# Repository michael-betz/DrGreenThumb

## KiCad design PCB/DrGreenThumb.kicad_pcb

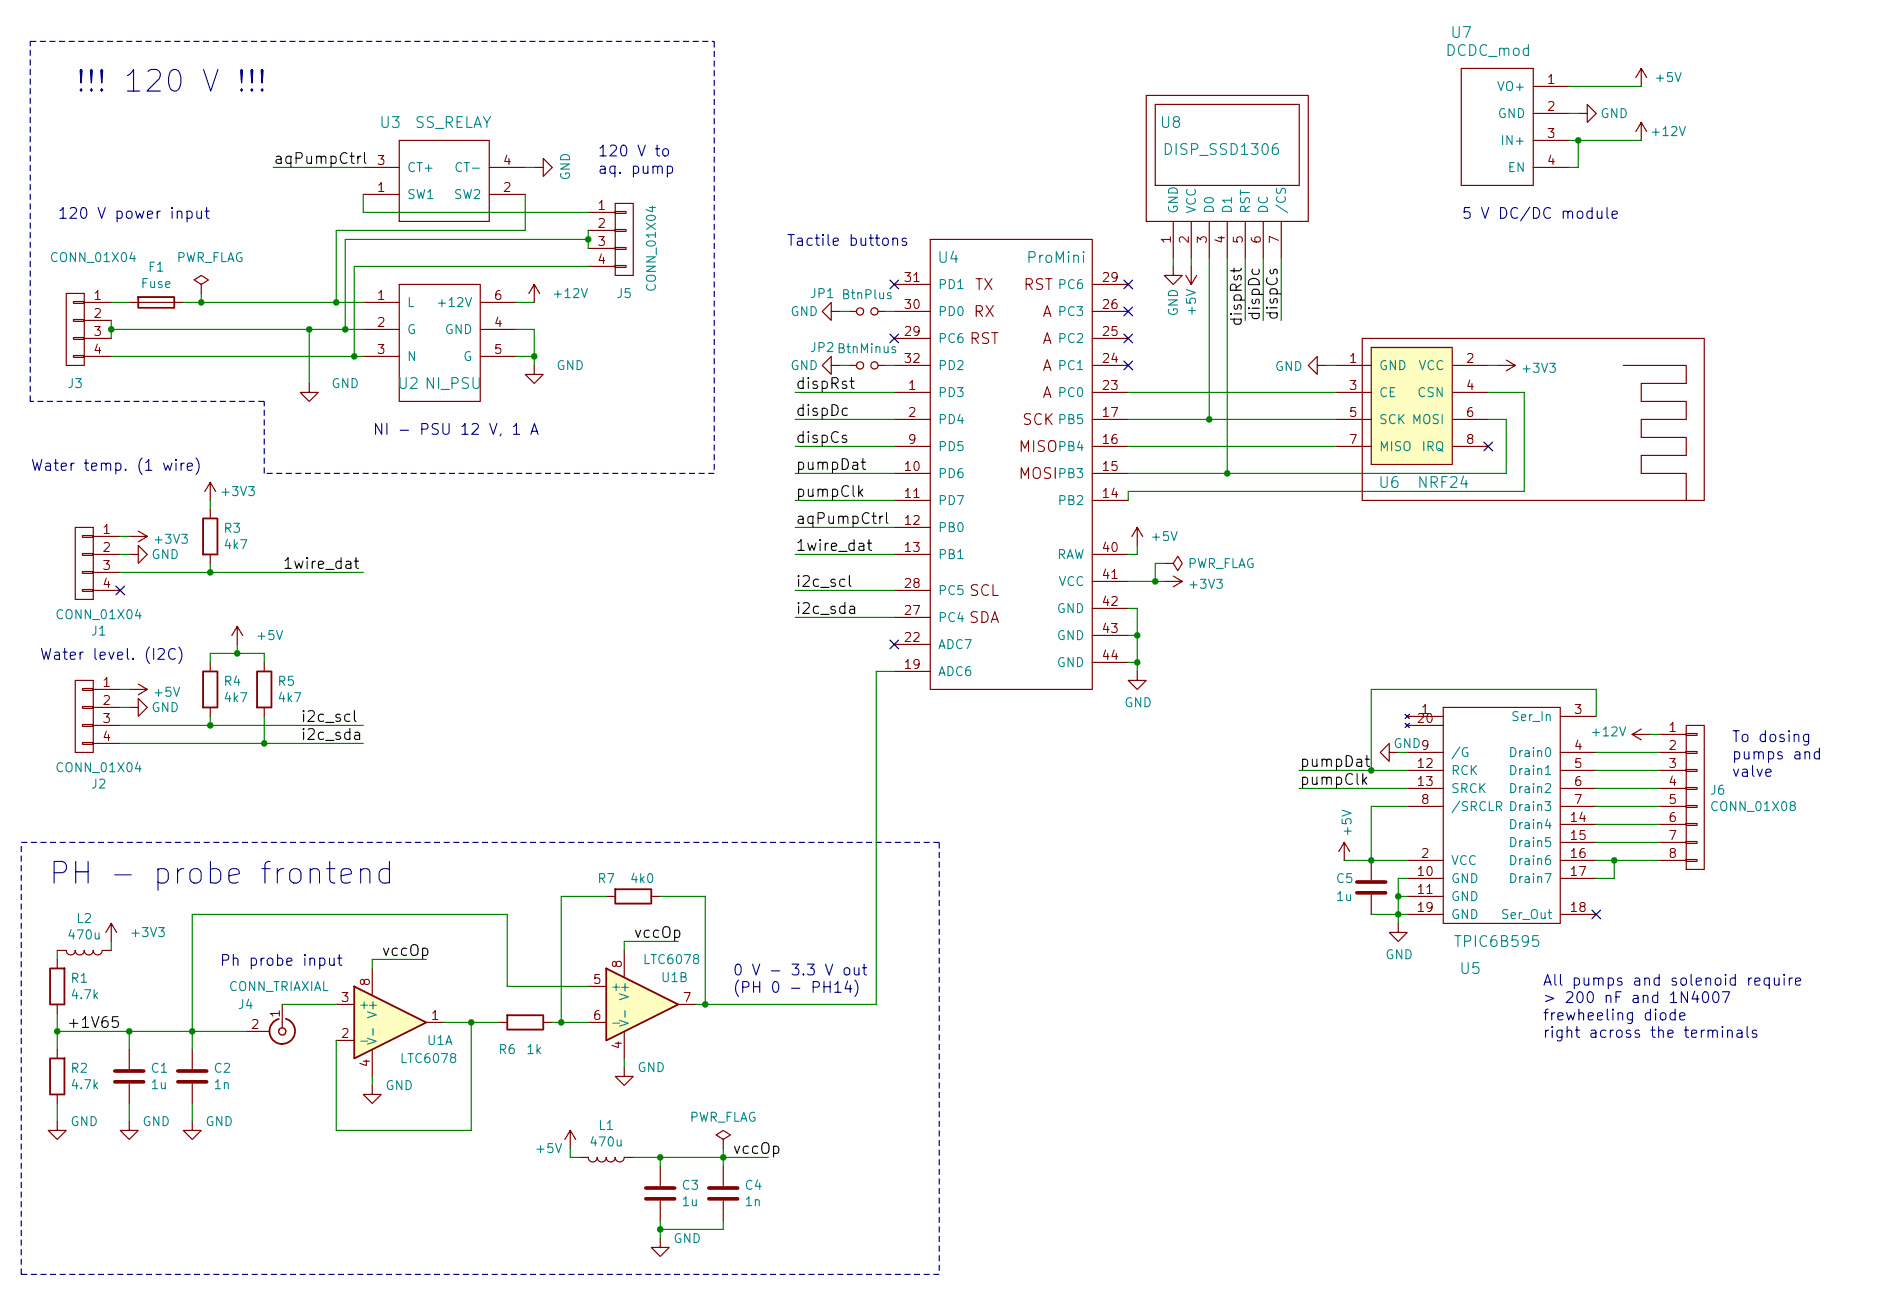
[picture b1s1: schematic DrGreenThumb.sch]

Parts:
C1, C3, C5: 1u; C_0805
C2, C4: 1n; C_0805
F1: Fuse; Fuseholder5x20_horiz_SemiClosed_Casing10x25mm
J1, J2, J3, J5: CONN_01X04; Pin_Header_Straight_1x04_Pitch2.54mm
J4: CONN_TRIAXIAL; bnc-ci
J6: CONN_01X08; Pin_Header_Straight_1x08_Pitch2.54mm
JP1: BtnPlus; ITT_TACT
JP2: BtnMinus; ITT_TACT
L1, L2: 470u; R_1210_HandSoldering
R1, R2: 4.7k; R_0805
R3, R4, R5: 4k7; R_0805
R6: 1k; R_0805
R7: 4k0; R_0805
U1: LTC6078; MSOP-8_3x3mm_Pitch0.65mm
U2: NI_PSU
U3: SS_RELAY
U4: ProMini; PRO_MINI
U5: TPIC6B595; DIP-20_W7.62mm
U6: NRF24
U7: DCDC_mod; ebay_dcdc
U8: DISP_SSD1306

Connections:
+3V3: J1.1, L2.1, R3.1, U4.41 (VCC), U6.2 (VCC)
+5V: C5.1, J2.1, L1.2, R4.1, R5.1, U4.40 (RAW), U5.2 (VCC), U5.8 (/SRCLR), U7.1 (VO+), U8.2 (VCC)
+12V: J6.1, U2.6 (+12V), U7.3 (IN+), U7.4 (EN)
/1wire_dat: J1.3, R3.2, U4.13 (PB1)
/+1V65: C1.1, C2.1, J4.2 (Ext), R1.1, R2.2, U1.5 (+)
/aqPumpCtrl: U3.3 (CT+), U4.12 (PB0)
/dispCs: U4.9 (PD5), U8.7 (/CS)
/dispDc: U4.2 (PD4), U8.6 (DC)
/dispRst: U4.1 (PD3), U8.5 (RST)
/i2c_scl: J2.3, R4.2, U4.28 (PC5)
/i2c_sda: J2.4, R5.2, U4.27 (PC4)
/pumpClk: U4.11 (PD7), U5.13 (SRCK)
/pumpDat: U4.10 (PD6), U5.3 (Ser_In), U5.12 (RCK)
/vccOp: C3.1, C4.1, L1.1, U1.8 (V+)
GND: C1.2, C2.2, C3.2, C4.2, C5.2, J1.2, J2.2, J3.2, J3.3, J5.2, J5.3, JP1.1, JP2.1, R2.1, U1.4 (V-), U2.2 (G), U2.4 (GND), U2.5 (G), U3.4 (CT-), U4.42 (GND), U4.43 (GND), U4.44 (GND), U5.9 (/G), U5.10 (GND), U5.11 (GND), U5.19 (GND), U6.1 (GND), U7.2 (GND), U8.1 (GND)
unnamed: F1.1, U2.1 (L), U3.2 (SW2)
unnamed: F1.2, J3.1
unnamed: J3.4, J5.4, U2.3 (N)
unnamed: J4.1 (In), U1.3 (+)
unnamed: J5.1, U3.1 (SW1)
unnamed: J6.2, U5.4 (Drain0)
unnamed: J6.3, U5.5 (Drain1)
unnamed: J6.4, U5.6 (Drain2)
unnamed: J6.5, U5.7 (Drain3)
unnamed: J6.6, U5.14 (Drain4)
unnamed: J6.7, U5.15 (Drain5)
unnamed: J6.8, U5.16 (Drain6), U5.17 (Drain7)
unnamed: JP1.2, U4.30 (PD0)
unnamed: JP2.2, U4.32 (PD2)
unnamed: L2.2, R1.2
unnamed: R6.1, R7.2, U1.6 (-)
unnamed: R6.2, U1.1, U1.2 (-)
unnamed: R7.1, U1.7, U4.19 (ADC6)
unnamed: U4.14 (PB2), U6.4 (CSN)
unnamed: U4.15 (PB3), U6.6 (MOSI), U8.4 (D1)
unnamed: U4.16 (PB4), U6.7 (MISO)
unnamed: U4.17 (PB5), U6.5 (SCK), U8.3 (D0)
unnamed: U4.23 (PC0), U6.3 (CE)

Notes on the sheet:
Ph probe input
To dosing pumps and valve
Water temp. (1 wire)
120 V to aq. pump
5 V DC/DC module
Water level. (I2C)
120 V power input
NI - PSU 12 V, 1 A
!!! 120 V !!!
0 V - 3.3 V out (PH 0 - PH14)
PH - probe frontend
Tactile buttons
All pumps and solenoid require > 200 nF and 1N4007 frewheeling diode right across the terminals

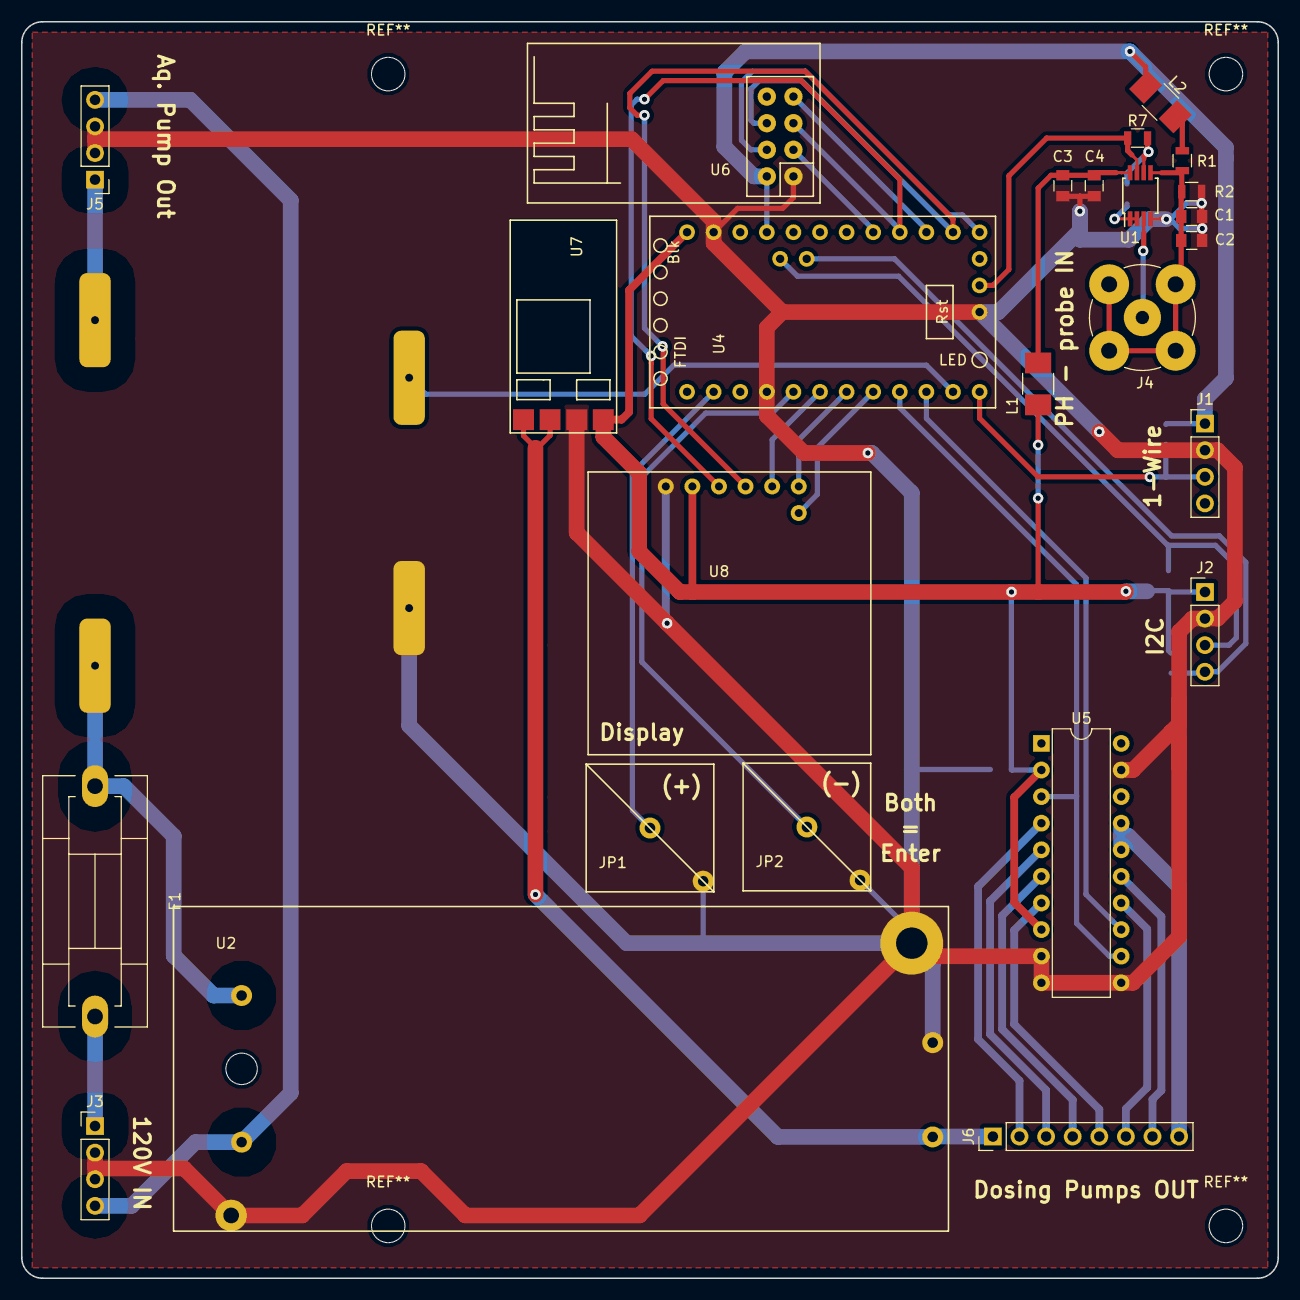
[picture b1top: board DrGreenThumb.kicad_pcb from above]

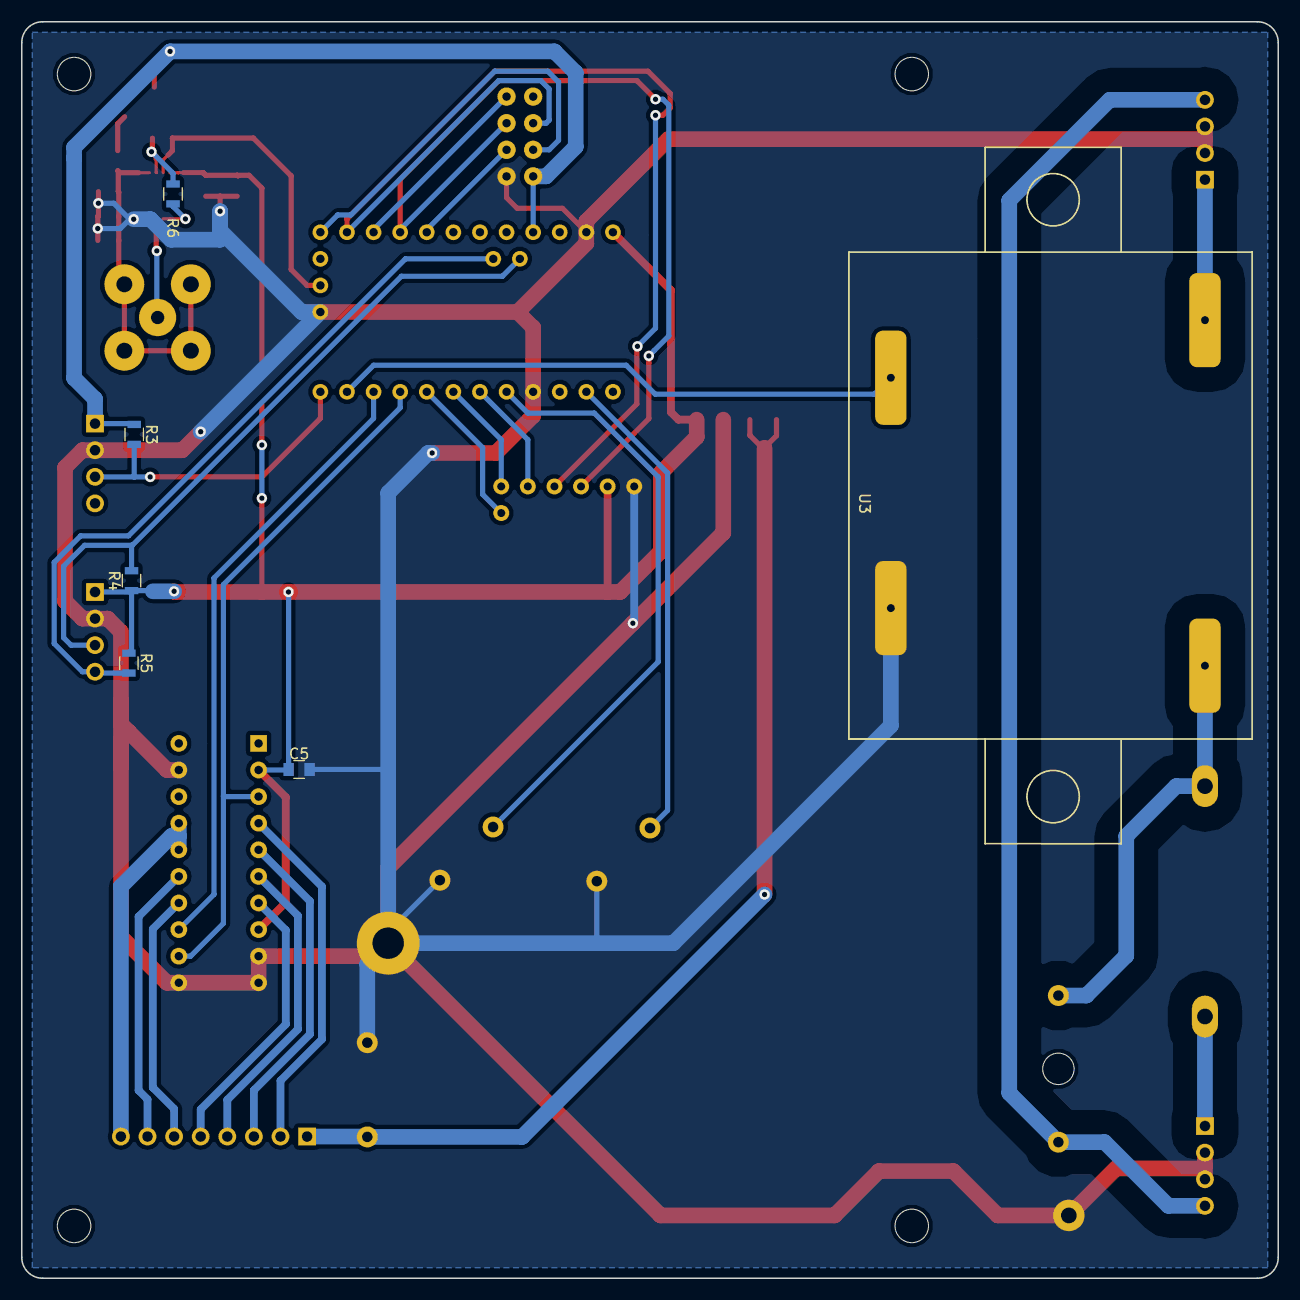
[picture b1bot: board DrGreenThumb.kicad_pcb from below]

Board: 2 copper layers, 120.0 x 120.0 mm, 31 parts (6 on the bottom side), 38 nets.

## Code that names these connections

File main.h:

/*
 * main.h
 *
 *  Created on: Apr 14, 2014
 *      Author: michael
 */

#ifndef MAIN_H_
#define MAIN_H_

//--------------------------------------------------
// Global Defines
//--------------------------------------------------
// GPIO
#define PIN_BTN1 		PD0
#define PIN_UART_TX		PD1
#define PIN_BTN2 		PD2
#define PIN_DISP_RST 	PD3
#define PIN_DISP_DC 	PD4	// Data / Command
#define PIN_DISP_CS 	PD5
#define PIN_PUMP_DAT 	PD6
#define PIN_PUMP_CLK 	PD7
#define PIN_SS_REL 		PB0
#define PIN_1WIRE_DAT 	PB1
#define PIN_NRF_CSN		PB2
#define PIN_SPI_MOSI	PB3
#define PIN_SPI_MISO	PB4
#define PIN_SPI_SCK		PB5
#define PIN_NRF_CE 		PC0
#define PIN_I2C_SDA 	PC4
#define PIN_I2C_SCL 	PC5

// Constants
#define BAUD 			38400	// Serial baudrate for user interface
#define TPIC_DELAY_US 	1
#define ADC_AVG_FACT 	6		//Sample 2^N times and average result
#define ADC_MUX_PH		6
#define ADC_MUX_TEMP	8
#define T_OFF			60*60*4	//Aquarium pump Off for 4 h
#define T_ON			60*5	//Aquarium pump ON for 5 min
#define DOSING_CHANNELS 7

// Flags
#define FLAG_PREQ_ON		0		//Requested to switch Pump ON
#define FLAG_PREQ_OFF		1		//Requested to switch Pump Off
#define FLAG_REPORT_STATUS 	2		//Report status over nRF24
#define FLAG_IS_DOSING		3		//A dosing pump is running
#define FLAG_IS_PUMP		4		//Main pump is running (reserved zero, only for report status)
#define FLAG_IS_RECIPE		5		//A recipe sequence is running

// Pseudo functions
#define SBI(reg, bit) 		( reg |=  ( 1 << bit ) )
#define CBI(reg, bit) 		( reg &= ~( 1 << bit ) )
#define IBI(reg, bit) 		( (reg&(1<<bit)) != 0 )
#define PUMP_ON()			{ SBI( PORTB, PIN_SS_REL ); }
#define PUMP_OFF()			{ CBI( PORTB, PIN_SS_REL ); }
#define IS_PUMP()			  IBI( PORTB, PIN_SS_REL )
#define SLEEP()				{ asm volatile("sleep"); }
#define SLEEP_SET_ADC()     { SMCR=0b00000011; }	//For ADC measurements
#define SLEEP_SET_IDLE()    { SMCR=0b00000001; }	//When T0 still needs to run
#define SLEEP_SET_STANDBY() { SMCR=0b00001101; }	//When only the crystal needs to run
#define SLEEP_SET_PDOWN() 	{ SMCR=0b00000101; }	//When everything except the WDT is off

//--------------------------------------------------
// Timer0 for timebase tick (stolen from Arduino)
//--------------------------------------------------
#define clockCyclesPerMicrosecond() ( F_CPU / 1000000L )
#define clockCyclesToMicroseconds(a) ( ((a) * 1000L) / (F_CPU / 1000L) )
#define T0_PRESCALE 1024
#define T0_RELOAD    244/2
#define MICROSECONDS_PER_TIMER0_OVERFLOW ( clockCyclesToMicroseconds(T0_PRESCALE*(T0_RELOAD+1L)) )
// the whole number of milliseconds per timer0 overflow
#define MILLIS_INC       (MICROSECONDS_PER_TIMER0_OVERFLOW / 1000)
// the fractional number of microseconds per timer0 overflow.
#define MILLIS_INC_FRACT (MICROSECONDS_PER_TIMER0_OVERFLOW % 1000)
extern volatile uint32_t g_Millis;	//Milisecond counter (dont touch!)
uint32_t millis();					//Return number of milliseconds since startup

//--------------------------------------------------
// Global Variables
//--------------------------------------------------
extern volatile uint8_t flags;

//--------------------------------------------------
// Functions
//--------------------------------------------------
void init(void);


#endif /* MAIN_H_ */

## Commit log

2017-06-24 ADC and pump driver works
2017-06-25 ADC averaging factor
2017-06-29 both pumps, adc and nRF24 works
2017-06-30 added good timer
2017-07-03 Added Kicad PCB files
2017-07-19 Fixed radical bug in mySPI_avr, always sendind with noAck
2017-07-24 Added water level reporting
2017-07-25 Water level now filtered and a fixed point float. Added basic dosing pump interface
2017-08-20 Added PH calibration worksheet
2017-09-17 Added the Recipe command (a series of dosing pulses)
